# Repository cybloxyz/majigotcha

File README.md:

# MAJIGOTCHA!

MAJIGOTCHA is a handheld digital pet in a small, bear head-shaped device. Users nurture a virtual creature from hatching through different life stages by feeding, cleaning, and playing with it using three buttons. Proper care determines its growth, while neglect can cause it to die.

## why MAJIGOTCHA?
can't afford the real tamagotchi? yeah that is why i build my own, it is not tamagotchi it is MAJIGOTCHA, it has my dream features such fingerprint and touch sensor, i make this because my sister is really dream to have a tamagotchi but since it is too expensive to buy i prefer make this by my self, since i want something more than just a tamagotchi.

## features

this is the first version of MAJIGOTCHA! it has really great features lemme break down:
> touch sensor, this mean you could pat your pet! tame it!

> fingerprint sensor, make it only yours..it will recognizes your fingerprint and can only be tamed with you.

> potentiometer scroll, since this MAJIGOTCHA has more complex features, the screen-menu could be navigate by potentiometer and button.

> in future i will upgrade this MAJIGOTCHA firmware to OTA and various casing.

## code example, pcb and schema
i made the case using [onshape](https://onshape.com) and here is the document link [MAJIGOTCHA-case](https://cad.onshape.com/documents/353c81332f9ae163598e6183/w/df33fd15e80ae307a4e30d2f/e/6c68072ba9f649a3b4a35ab0)
i am using RV09 vertical potentiometer so it will be solderen onPCB and for things such OLED, TTP223, HLK-ZW101 i use pinHeader 2.54 instead

in this schema i'm using global labels since it is easier to understand and to read, for the PCB it is 2 layer, and contain vias, the pcb's size is not more than 50mmx50mm which it resulting in cheaper price.

this MAJIGOTCHA is similar to tamagotchi BUT it is has more unique features, in here every stats even tame, inTamingProgress or notTame is has it own sprite, here is the bitmaps example:
```
const unsigned char PROGMEM notTame[] = {
  0b00000000, 0b00000000,
  0b00000000, 0b00000000,
  0b00001100, 0b01100000,
  0b00010011, 0b10010000,
  0b00010000, 0b00010000,
  0b00100100, 0b01001000,
  0b00010010, 0b10010000,
  0b00010000, 0b00010000,
  0b00001000, 0b00100000,
  0b00000111, 0b11000000,
  0b00001000, 0b00100000,
  0b00010100, 0b01010000,
  0b00010010, 0b10010000,
  0b00001100, 0b01100000,
  0b00010011, 0b10010000,
  0b00001100, 0b01100000
};
```
in notTame stat it means you rarely identify your fingerprint and interact with him, remember it is only you and some of your friends fingerprint! other than that he will very very badMood!
```
const unsigned char PROGMEM curious[] = {
  0b00000000, 0b00000000,
  0b00000000, 0b00000000,
  0b00001100, 0b01100000,
  0b00010011, 0b10010000,
  0b00010000, 0b00010000,
  0b00001010, 0b10100000,
  0b00010010, 0b10010000,
  0b00010000, 0b00010000,
  0b00001000, 0b00100000,
  0b00000111, 0b11000000,
  0b00001000, 0b00100000,
  0b00010100, 0b01010000,
  0b00010010, 0b10010000,
  0b00001100, 0b01100000,
  0b00010011, 0b10010000,
  0b00001100, 0b01100000
};
```
curious stat is when his tame progress is around 50 like more than 30 but less than 50, he starts curious with you! keep interact with him until he is happy!
```
const unsigned char PROGMEM happy[] = {
  0b00000000, 0b00000000,
  0b00000000, 0b00000000,
  0b00001100, 0b01100000,
  0b00010011, 0b10010000,
  0b00010000, 0b00010000,
  0b00001010, 0b10100000,
  0b00010001, 0b00010000,
  0b00010000, 0b00010000,
  0b00001000, 0b00100000,
  0b00000111, 0b11000000,
  0b00001000, 0b00100000,
  0b00010100, 0b01010000,
  0b00010010, 0b10010000,
  0b00001100, 0b01100000,
  0b00010011, 0b10010000,
  0b00001100, 0b01100000
};
```
if you reached happy! it means he likes you so much and he is happy to be with you! keep it like this and you both will be good friends!

## components
| no    | name  | qty | price in idr |
|-------|------------------------------------------------------------------------------------------------------------------------------------------------------------------------------------------------------------------------------------------------------------------------------------------------------------------------------------------------------------------------------|-----|--------------|
| 1     | [seeeduino xiao esp32-c6](https://shopee.co.id/Pre-Soldered-Seeeduino-Xiao-ESP32-C3-C6-S3-nRF52840-Mini-Development-Board-wifi-module-bluetooth5.0-i.1733652584.44605902551?extraParams=%7B%22display_model_id%22%3A315532221124%2C%22model_selection_logic%22%3A3%7D&sp_atk=1e86e1a1-d50f-4ddf-872c-1a7bf0063a2c&xptdk=1e86e1a1-d50f-4ddf-872c-1a7bf0063a2c)                | 1   | 125000       |
| 2     | [OLED 1.3inch 4 pin](https://shopee.co.id/Oled-1.3-inch-White-128X64-LCD-LED-Display-I2C-SPI-i.29614947.15299206834?extraParams=%7B%22display_model_id%22%3A286380108800%2C%22model_selection_logic%22%3A2%7D&sp_atk=5581b29f-11be-4425-b561-856e9085b63b&xptdk=5581b29f-11be-4425-b561-856e9085b63b)                                                                        | 1   | 60000        |
| 3     | [LiPo battery 1000mAh 3.7V](https://shopee.co.id/Baterai-lithium-polimer-1000mah-523450-1500mah-803450-i.6828741.7404713970?extraParams=%7B%22display_model_id%22%3A200235569624%2C%22model_selection_logic%22%3A2%7D&sp_atk=97c69378-6d19-4a8a-8440-88d717dd88a4&xptdk=97c69378-6d19-4a8a-8440-88d717dd88a4)                                                                | 1   | 70000        |
| 4     | [SW Push Tactile button](https://shopee.co.id/Tombol-Reset-saklar-Tactile-Push-Button-Micro-Switch-6x6-mm-4Pin-DIP-i.7849796.24862806415?extraParams=%7B%22display_model_id%22%3A99512365459%2C%22model_selection_logic%22%3A2%7D&sp_atk=b424789e-79b1-47b6-bc5c-de19a421847f&xptdk=b424789e-79b1-47b6-bc5c-de19a421847f)                                                    | 3   | 12000        |
| 5     | [RV09 20k Potentiometer](https://shopee.co.id/Potentiometer-Potensiometer-RV09-potensio-Mono-1-2-5-10-20-50-100-K-i.48406045.22301052102?extraParams=%7B%22display_model_id%22%3A230048446464%2C%22model_selection_logic%22%3A3%7D&sp_atk=1b9f26a0-71eb-4422-b890-36847dca0c69&xptdk=1b9f26a0-71eb-4422-b890-36847dca0c69)                                                   | 1   | 8000         |
| 6     | [TP223 capacitive touch sensor](https://shopee.co.id/MERAH-Saklar-Sentuh-Touch-Sensor-Capacitive-TTP223-Switch-Arduino-i.6406600.1153531563?extraParams=%7B%22display_model_id%22%3A41163384882%2C%22model_selection_logic%22%3A3%7D&sp_atk=5572a8bb-4cf4-4d05-ab05-ae396874a5bd&xptdk=5572a8bb-4cf4-4d05-ab05-ae396874a5bd)                                                 | 1   | 2000         |
| 7     | [HLK-ZW101 capacitive fingerprint](https://shopee.co.id/modul-fingerprint-capacitive-fingerprint-sensor-modul-kapasitas-50-profil-sidik-jari-support-arduino-esp32-i.108345327.28986833146?extraParams=%7B%22display_model_id%22%3A280149142816%2C%22model_selection_logic%22%3A3%7D&sp_atk=1f3d0cd1-fd72-4985-a735-fcf4e80ae198&xptdk=1f3d0cd1-fd72-4985-a735-fcf4e80ae198) | 1   | 120000       |
| 8     | [2.54 pin header](https://shopee.co.id/PIN-HEADER-MALE-STRIP-SINGLE-ROW-1X40-2.54MM-BLACK-HITAM-FOR-ARDUINO-MINI-NANO-i.62956347.5909650283?extraParams=%7B%22display_model_id%22%3A181542147744%2C%22model_selection_logic%22%3A2%7D&sp_atk=9b956594-5a8c-426c-a2a4-4f187335748b&xptdk=9b956594-5a8c-426c-a2a4-4f187335748b)                                                | 40  | 10000        |
| 9     | [female to female cable](https://shopee.co.id/Kabel-Jumper-40PCS-20CM-Male-to-Female-Female-to-Female-Male-to-Male-Dupont-%E2%80%93-Kabel-Koneksi-untuk-Breadboard-i.62956347.1063975553?extraParams=%7B%22display_model_id%22%3A270485393609%2C%22model_selection_logic%22%3A2%7D&sp_atk=fc82f2e6-d9de-483c-b11d-0f5a3227d0cb&xptdk=fc82f2e6-d9de-483c-b11d-0f5a3227d0cb)   | 40  | 10000        |
| 10    | [passive piezoelectric buzzer](https://shopee.co.id/Passive-Buzzer-3-12V-16-Ohm-BAGUS-12X8.5-mm-Pasive-Buzer-Pasif-Buser-i.193335132.52301383875?extraParams=%7B%22display_model_id%22%3A109588483742%2C%22model_selection_logic%22%3A3%7D&sp_atk=e76a41ab-416d-4e86-8c9f-0587ee075cda&xptdk=e76a41ab-416d-4e86-8c9f-0587ee075cda)                                           | 1   | 2000         |
| 11    | [female pin header (pin socket)](https://shopee.co.id/1x40p-Female-Pin-Header-2.54mm-40-Pin-Single-Row-PCB-Connector-Betina-i.6406600.1153531501?extraParams=%7B%22display_model_id%22%3A41163261938%2C%22model_selection_logic%22%3A3%7D&sp_atk=af0e8d18-340d-418a-b709-74f619aaadf8&xptdk=af0e8d18-340d-418a-b709-74f619aaadf8)                                            | 20  | 10000        |
| 12    | [connector XH2P housing](https://shopee.co.id/CONNECTOR-XH2.54-4P-PIN-FEMALE-20CM-CABLE-JST-2.54MM-SOCKET-CON-STOCKO-i.62956347.23700082559?extraParams=%7B%22display_model_id%22%3A49121904954%2C%22model_selection_logic%22%3A2%7D&sp_atk=69be3aae-f4b3-48a3-bb47-8a4b6dcf66db&xptdk=69be3aae-f4b3-48a3-bb47-8a4b6dcf66db)                                                 | 20  | 10000        |
| 13    | [jlcpcb](https://jlcpcb.com)                                                                                                                                                                                                                                                                                                                                                 | 5   | 65000        |
| 14    | [case](https://shopee.co.id/Jasa-Cetak-3D-Print-PLA-PLA-PETG-ABS-TPU-Nylon-Carbon-Fiber-Multicolor-Polycarbonate-Resin-i.81557195.43001716747?extraParams=%7B%22display_model_id%22%3A265141036120%2C%22model_selection_logic%22%3A3%7D&sp_atk=bbc55b01-5719-43ed-ab66-7336188997fe&xptdk=bbc55b01-5719-43ed-ab66-7336188997fe)                                              | 1   | 40000        |
| total | Rp.544.000

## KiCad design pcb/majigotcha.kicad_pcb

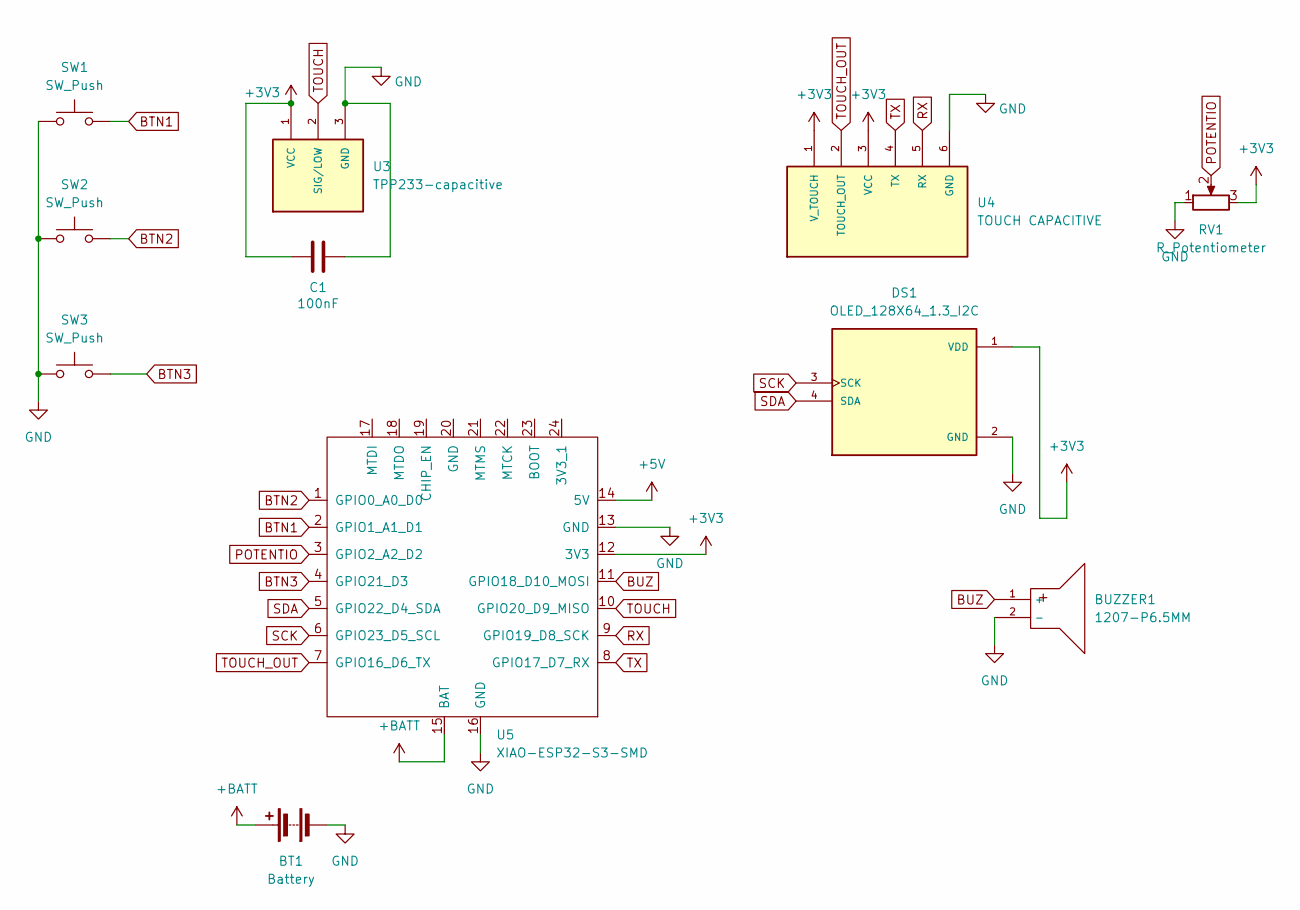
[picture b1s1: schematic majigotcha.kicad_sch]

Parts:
BT1: Battery; PinHeader_1x02_P2.54mm_Vertical
BUZZER1: 1207-P6.5MM; PinSocket_1x02_P2.54mm_Vertical; LCSC C49246964
C1: 100nF; C_0201_0603Metric_Pad0.64x0.40mm_HandSolder
DS1: OLED_128X64_1.3_I2C; PinSocket_1x04_P2.54mm_Vertical; PARTREV NA
RV1: R_Potentiometer; Potentiometer_Alpha_RD901F-40-00D_Single_Vertical
SW1, SW2, SW3: SW_Push; SW_PUSH_6mm_H5mm
U3: TPP233-capacitive; PinHeader_1x03_P2.54mm_Vertical; DigiKey_Part_Number 1738-1041-ND
U4: TOUCH CAPACITIVE; PinHeader_1x06_P2.54mm_Vertical; DigiKey_Part_Number 1738-1041-ND
U5: XIAO-ESP32-S3-SMD; XIAO-ESP32C6-SMD

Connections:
+3V3: C1.1, DS1.1 (VDD), RV1.3, U3.1 (VCC), U4.1 (V_TOUCH), U4.3 (VCC), U5.12 (3V3)
+5V: U5.14 (5V)
+BATT: BT1.1 (+), U5.15 (BAT)
BTN1: SW1.2, U5.2 (GPIO1_A1_D1)
BTN2: SW2.2, U5.1 (GPIO0_A0_D0)
BTN3: SW3.2, U5.4 (GPIO21_D3)
BUZ: BUZZER1.1 (+), U5.11 (GPIO18_D10_MOSI)
GND: BT1.2 (-), BUZZER1.2 (-), C1.2, DS1.2 (GND), RV1.1, SW1.1, SW2.1, SW3.1, U3.3 (GND), U4.6 (GND), U5.13 (GND), U5.16 (GND)
POTENTIO: RV1.2, U5.3 (GPIO2_A2_D2)
RX: U4.5 (RX), U5.9 (GPIO19_D8_SCK)
SCK: DS1.3 (SCK), U5.6 (GPIO23_D5_SCL)
SDA: DS1.4 (SDA), U5.5 (GPIO22_D4_SDA)
TOUCH: U3.2 (SIG/LOW), U5.10 (GPIO20_D9_MISO)
TOUCH_OUT: U4.2 (TOUCH_OUT), U5.7 (GPIO16_D6_TX)
TX: U4.4 (TX), U5.8 (GPIO17_D7_RX)

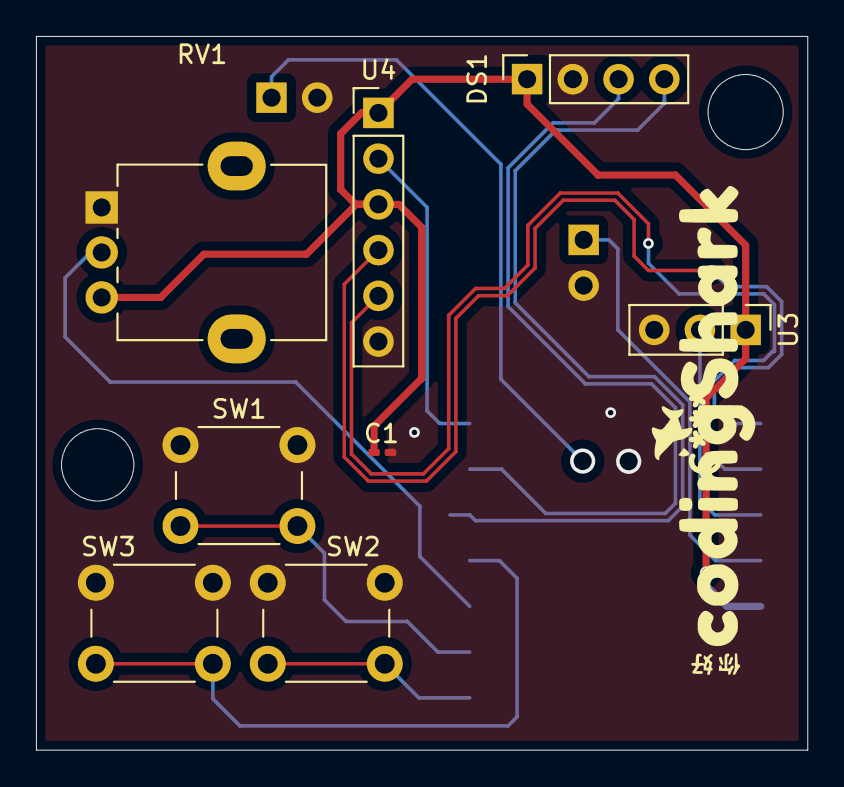
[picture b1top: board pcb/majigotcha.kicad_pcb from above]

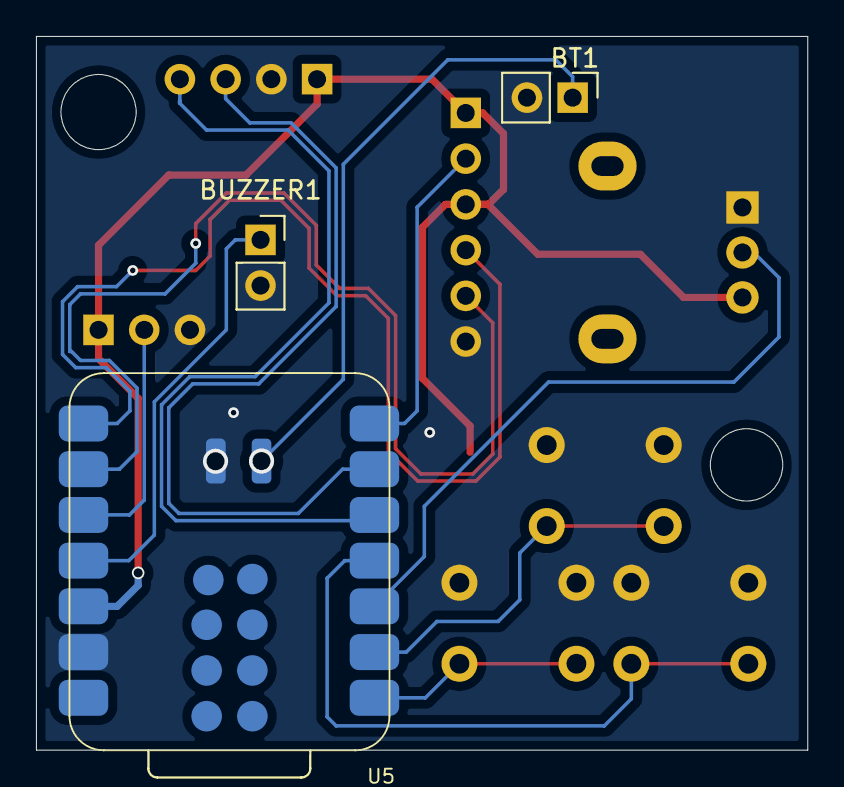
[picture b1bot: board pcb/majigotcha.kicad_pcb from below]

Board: 2 copper layers, 42.8 x 39.6 mm, 11 parts (3 on the bottom side), 14 nets.

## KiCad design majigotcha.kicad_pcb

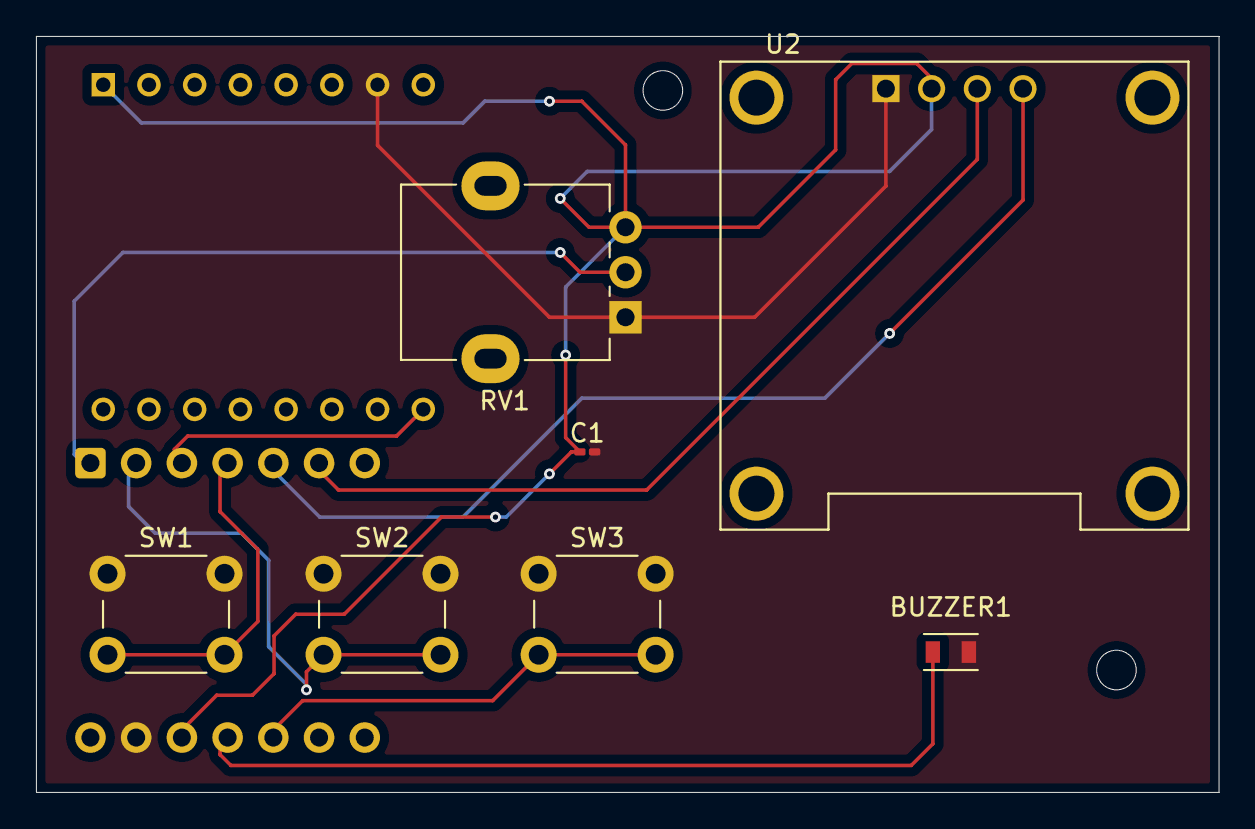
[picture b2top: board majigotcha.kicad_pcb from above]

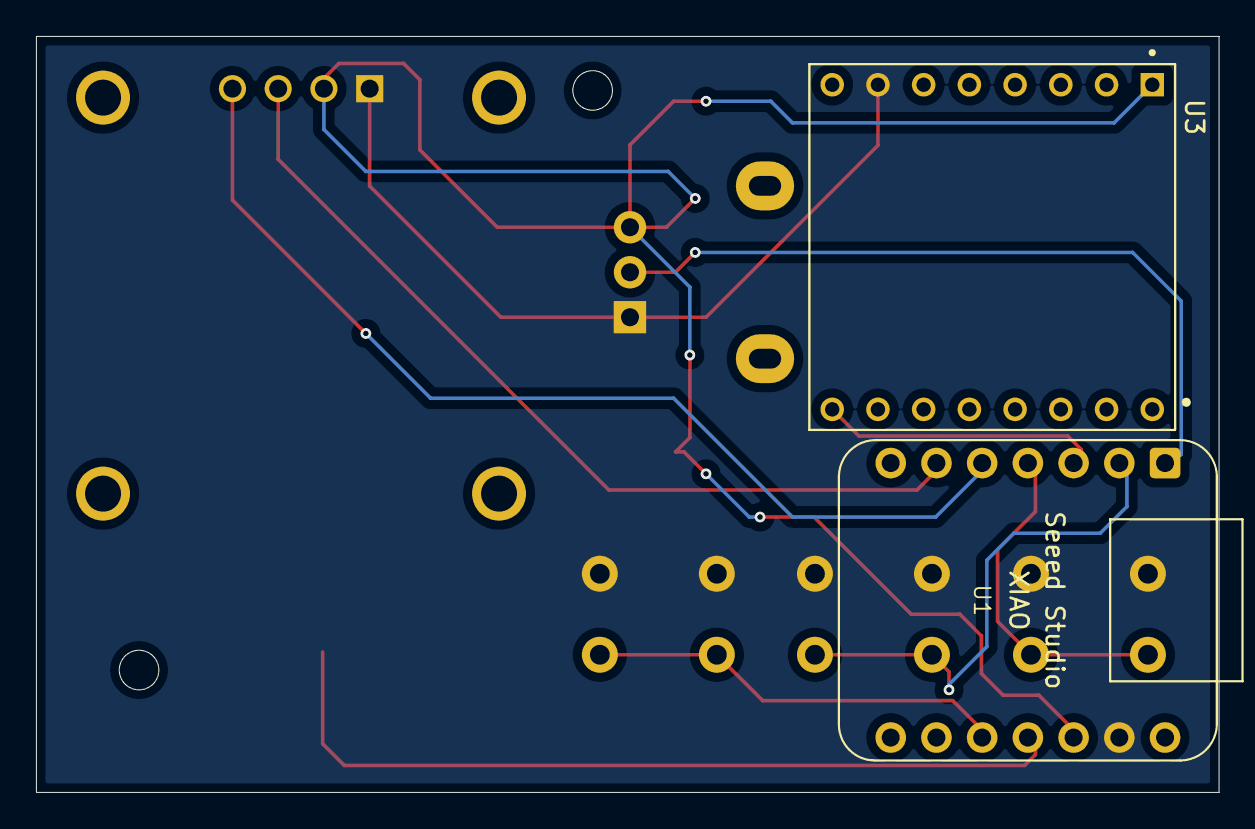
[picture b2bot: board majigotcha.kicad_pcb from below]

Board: 2 copper layers, 65.7 x 42.0 mm, 10 parts (2 on the bottom side), 10 nets.

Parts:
BUZZER1: 1207-P6.5MM; C49246964_BUZ-TH_BD12_5-P6_50-D1_4
C1: 100nF; C_0201_0603Metric_Pad0.64x0.40mm_HandSolder
RV1: R_Potentiometer; Potentiometer_Alpha_RD901F-40-00D_Single_Vertical
SW1, SW2, SW3: SW_Push; SW_PUSH_6mm
U1: XIAO-ESP32-C6; XIAO-Generic-Hybrid-14P-2.54-21X17.8MM
U2: DM-OLED096-636; MODULE_DM-OLED096-636
U3: TPP233-IC; MODULE_DFR0299
U4: TOUCH CAPACITIVE; Untitled

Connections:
+3V3: C1.1, RV1.3, U1.12 (3V3), U2.2 (VCC_IN), U3.1 (VCC)
/BTN1: SW1.2, U1.4 (GPIO21/D3)
/BTN2: SW2.2, U1.2 (GPIO1/A1/D1)
/BTN3: SW3.2, U1.10 (GPIO20/D9/MISO)
/POTENTIO: RV1.2, U1.1 (GPIO0/A0/D0)
/SCL: U1.6 (GPIO23/D5/SCL), U2.3 (SCL)
/SDA: U1.5 (GPIO22/D4/SDA), U2.4 (SDA)
/TOUCH: U1.3 (GPIO2/A2/D2), U3.9 (SIG/LOW)
GND: BUZZER1.2 (-), C1.2, RV1.1, SW1.1, SW2.1, SW3.1, U1.13 (GND), U2.1 (GND), U3.7 (GND)
unnamed: BUZZER1.1 (+), U1.11 (GPIO18/D10/MOSI)

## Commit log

2026-05-01 finish the pcb
2026-05-10 add firmware! oh and change of pcb wiring
2026-05-10 add README.md
2026-05-10 add stl file
2026-05-10 i forgot to add picture
2026-05-10 update gerbers
2026-05-11 add 0.3mm tolerance
2026-05-11 add via in pad
2026-05-13 add zine pages
2026-05-13 fix the links
2026-05-13 still fix links
